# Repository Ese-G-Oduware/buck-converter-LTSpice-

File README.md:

# 12V to 5V Step Down Buck Converter (LTSpice & KiCad PCB)
This is an asynchronous buck converter that steps down 12V to 5V, designed and simulates in LTSpice using the LTC4440 (IC) high-side gate driver with a bootstrap circuit.
| KiCad Schematic | LTSpice Schematic |
| :---: | :---: |
|  |  |

## Key Specifications
* **Input Voltage ($V_{in}$):** 12V DC
* **Output Voltage ($V_{out}$):** ~4.8V DC (Steady-State)
* **Load Current ($I_{out}$):** 1A (5Ω Load)
* **Switching Frequency ($f_{sw}$):** 100 kHz (41.67% Duty Cycle)
* **Output Ripple ($\Delta V_{out}$):** ~39 mV (< 1%)
* **PCB Architecture:** 2-layer board optimized for high-frequency switching and low EMI

## Design Calculations
* **Duty Cycle:** $D = V_{out} / V_{in} = 5V / 12V = 41.67\%$
* **Inductor:** $L = \frac{(V_{in} - V_{out}) \cdot T_{on}}{\Delta I_L} = \frac{(12 - 5) \cdot 4.17\mu s}{0.3A} \approx 97.3\mu H \rightarrow 100\mu H$
* **High-Side MOSFET Drive:** Utilizes the LTC4440 high-speed driver paired with a bootstrap diode and capacitor ($C_{boot} = 100\text{nF}$) to elevate gate voltage above the floating switching node.

## Simulation & Results

* **Startup Phase:** Displays natural LC filter settling overshoot peaking at 6.5V.
* **Non-Idealities:** Steady-state output settles slightly below theoretical 5V at 4.8V due to MOSFET $R_

## PCB Layout & Manufacturing

* **Compact Switching Loop:** Components positioned to minimize power loop area to reduce parasitic inductance and switching noise.
* **Thermal Management:** Integrated ground plane pours for efficient heat dissipation across components.
* **DRC Verification:** Passed full KiCad Design Rule Checks.

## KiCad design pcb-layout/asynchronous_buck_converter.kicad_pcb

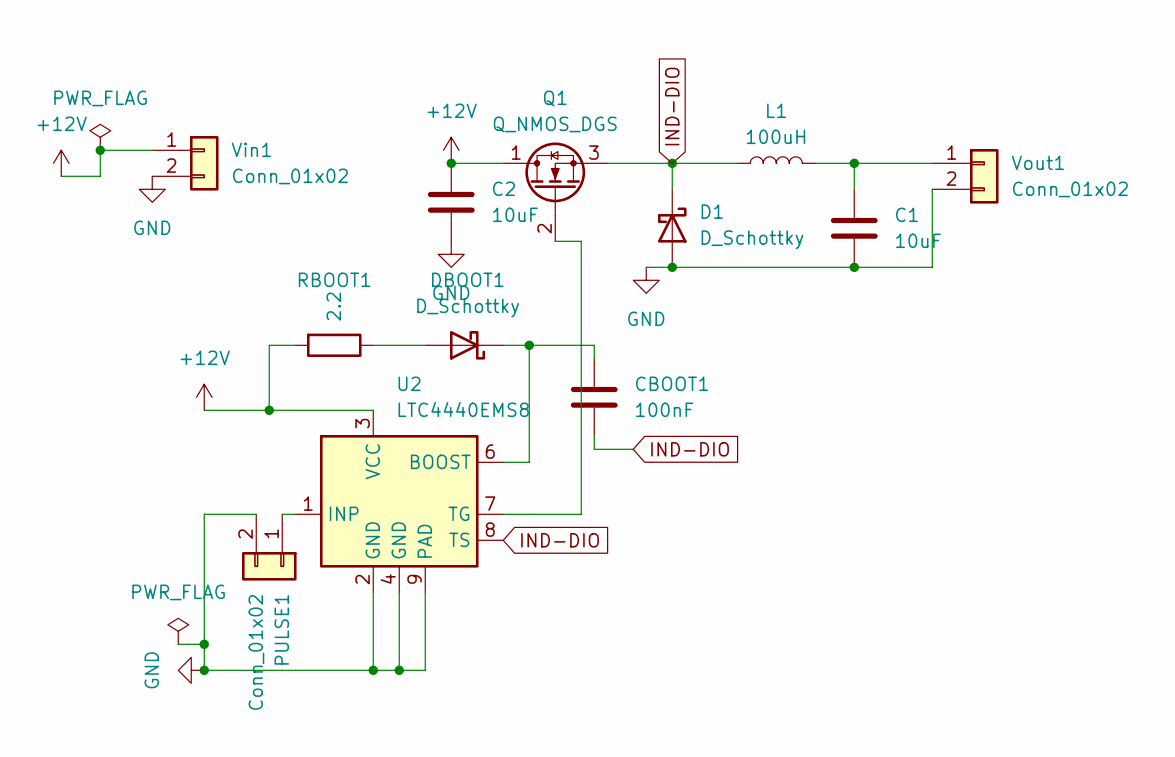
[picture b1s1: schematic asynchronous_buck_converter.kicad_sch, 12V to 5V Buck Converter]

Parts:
C1, C2: 10uF; C_1206_3216Metric
CBOOT1: 100nF; C_0805_2012Metric
D1: D_Schottky; D_SMA
DBOOT1: D_Schottky; D_SOD-123
L1: 100uH; L_7.3x7.3_H3.5
PULSE1: Conn_01x02; TerminalBlock_Phoenix_PT-1,5-2-5.0-H_1x02_P5.00mm_Horizontal
Q1: Q_NMOS_DGS; TO-252-2
RBOOT1: 2.2; R_0805_2012Metric
U2: LTC4440EMS8; MSOP-8-1EP_3x3mm_P0.65mm_EP1.68x1.88mm
Vin1: Conn_01x02; TerminalBlock_Phoenix_PT-1,5-2-5.0-H_1x02_P5.00mm_Horizontal
Vout1: Conn_01x02; TerminalBlock_Phoenix_PT-1,5-2-5.0-H_1x02_P5.00mm_Horizontal

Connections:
+12V: C2.1, Q1.1 (D), RBOOT1.2, U2.3 (VCC), Vin1.1
GND: C1.2, C2.2, D1.2 (A), PULSE1.2, U2.2 (GND), U2.4 (GND), U2.9 (PAD), Vin1.2, Vout1.2
IND-DIO: CBOOT1.2, D1.1 (K), L1.1, Q1.3 (S), U2.8 (TS)
unnamed: DBOOT1.2 (A), RBOOT1.1
unnamed: CBOOT1.1, DBOOT1.1 (K), U2.6 (BOOST)
unnamed: PULSE1.1, U2.1 (INP)
unnamed: Q1.2 (G), U2.7 (TG)
unnamed: C1.1, L1.2, Vout1.1

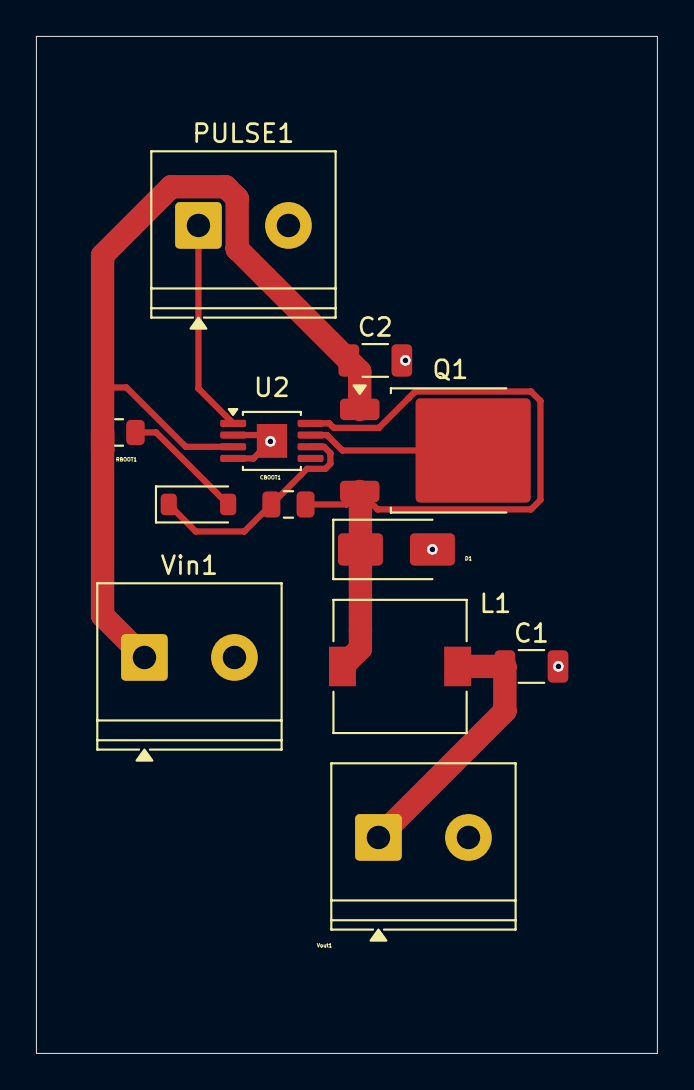
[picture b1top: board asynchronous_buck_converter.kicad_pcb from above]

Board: 2 copper layers, 34.5 x 56.5 mm, 12 parts (0 on the bottom side), 8 nets.
